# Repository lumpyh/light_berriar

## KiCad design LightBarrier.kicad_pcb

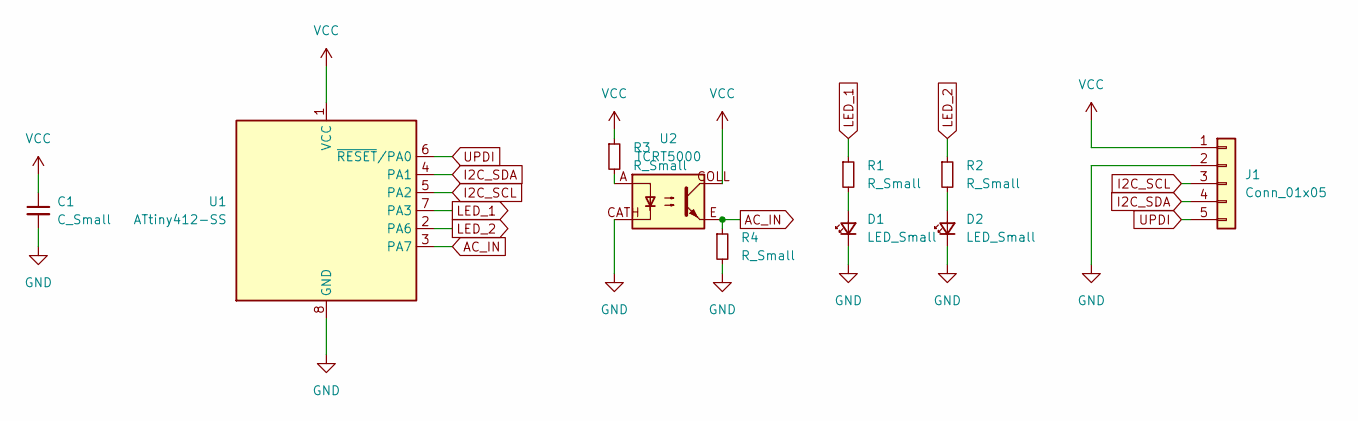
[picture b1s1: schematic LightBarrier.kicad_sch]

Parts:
C1: C_Small; C_2225_5664Metric
D1, D2: LED_Small; LED_1206_3216Metric
J1: Conn_01x05; PinHeader_1x05_P2.54mm_Vertical
R1, R2, R3, R4: R_Small; R_1206_3216Metric
U1: ATtiny412-SS; SOIC-8_3.9x4.9mm_P1.27mm
U2: TCRT5000; tcrt5000

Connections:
AC_IN: R4.1, U1.3 (PA7), U2.E
GND: C1.2, D1.1 (K), D2.1 (K), J1.2, R4.2, U1.8 (GND), U2.CATH
I2C_SCL: J1.3, U1.5 (PA2)
I2C_SDA: J1.4, U1.4 (PA1)
LED_1: R1.1, U1.7 (PA3)
LED_2: R2.1, U1.2 (PA6)
unnamed: D1.2 (A), R1.2
unnamed: D2.2 (A), R2.2
unnamed: R3.2, U2.A
UPDI: J1.5, U1.6 (~RESET/PA0)
VCC: C1.1, J1.1, R3.1, U1.1 (VCC), U2.COLL

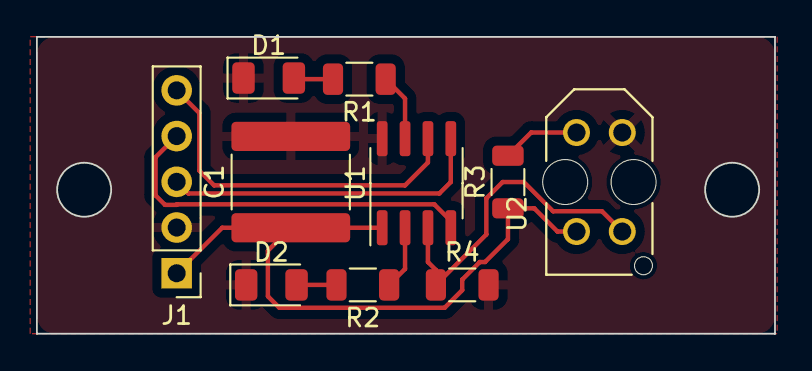
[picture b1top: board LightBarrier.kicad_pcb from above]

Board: 2 copper layers, 41.0 x 16.5 mm, 10 parts (0 on the bottom side), 11 nets.

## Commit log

2023-11-30 inital design
